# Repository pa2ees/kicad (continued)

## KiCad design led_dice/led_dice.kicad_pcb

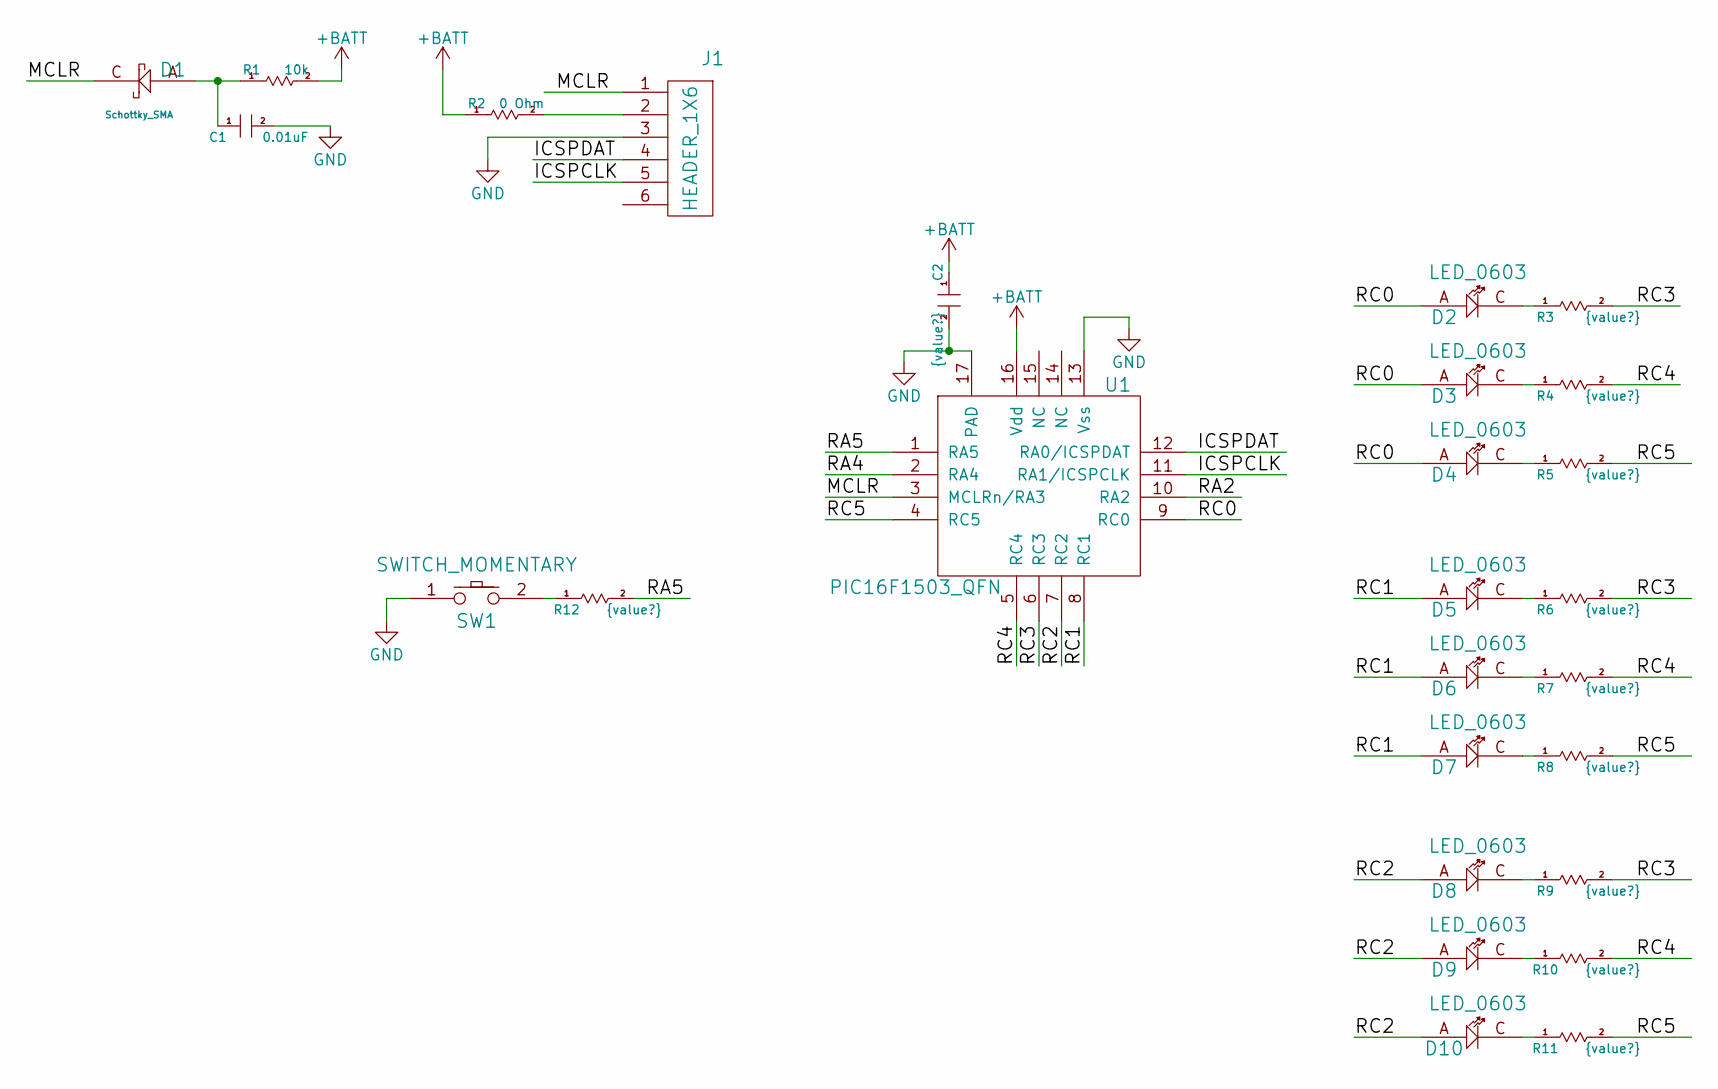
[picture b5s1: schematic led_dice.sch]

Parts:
C1: CAP_0603; C0603
C2: CAP_0603; C0603; MFG_PN {PN}
D1: Schottky_SMA; SMA; MFG_PN {PN}
D2, D3, D4, D5, D6, D7, D8, D9, D10: LED_0603; D0603; MFG_PN {PN}
J1: HEADER_1X6; Header_6-pin_100mil
R1, R2: RES_0603; R0603
R3, R4, R5, R6, R7, R8, R9, R10, R11, R12: RES_0603; R0603; MFG_PN {PN}
SW1: SWITCH_MOMENTARY; TACT-SW_6x6
U1: PIC16F1503_QFN; MFG_PN PIC16F1503-I/MG

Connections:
+BATT: C2.1, R1.2, R2.1, U1.16 (Vdd)
/ICSPCLK: J1.5, U1.11 (RA1/ICSPCLK)
/ICSPDAT: J1.4, U1.12 (RA0/ICSPDAT)
/MCLR: D1.C, J1.1, U1.3 (MCLRn/RA3)
/RA2: U1.10 (RA2)
/RA4: U1.2 (RA4)
/RA5: R12.2, U1.1 (RA5)
/RC0: D2.A, D3.A, D4.A, U1.9 (RC0)
/RC1: D5.A, D6.A, D7.A, U1.8 (RC1)
/RC2: D8.A, D9.A, D10.A, U1.7 (RC2)
/RC3: R3.2, R6.2, R9.2, U1.6 (RC3)
/RC4: R4.2, R7.2, R10.2, U1.5 (RC4)
/RC5: R5.2, R8.2, R11.2, U1.4 (RC5)
GND: C1.2, C2.2, J1.3, SW1.1, U1.13 (Vss), U1.17 (PAD)
unnamed: C1.1, D1.A, R1.1
unnamed: D2.C, R3.1
unnamed: D3.C, R4.1
unnamed: D4.C, R5.1
unnamed: D5.C, R6.1
unnamed: D6.C, R7.1
unnamed: D7.C, R8.1
unnamed: D8.C, R9.1
unnamed: D9.C, R10.1
unnamed: D10.C, R11.1
unnamed: J1.2, R2.2
unnamed: R12.1, SW1.2

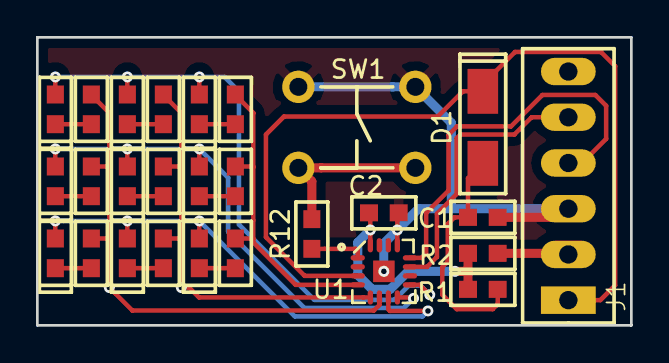
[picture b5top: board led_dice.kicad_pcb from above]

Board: 2 copper layers, 33.0 x 16.0 mm, 27 parts (0 on the bottom side), 24 nets.

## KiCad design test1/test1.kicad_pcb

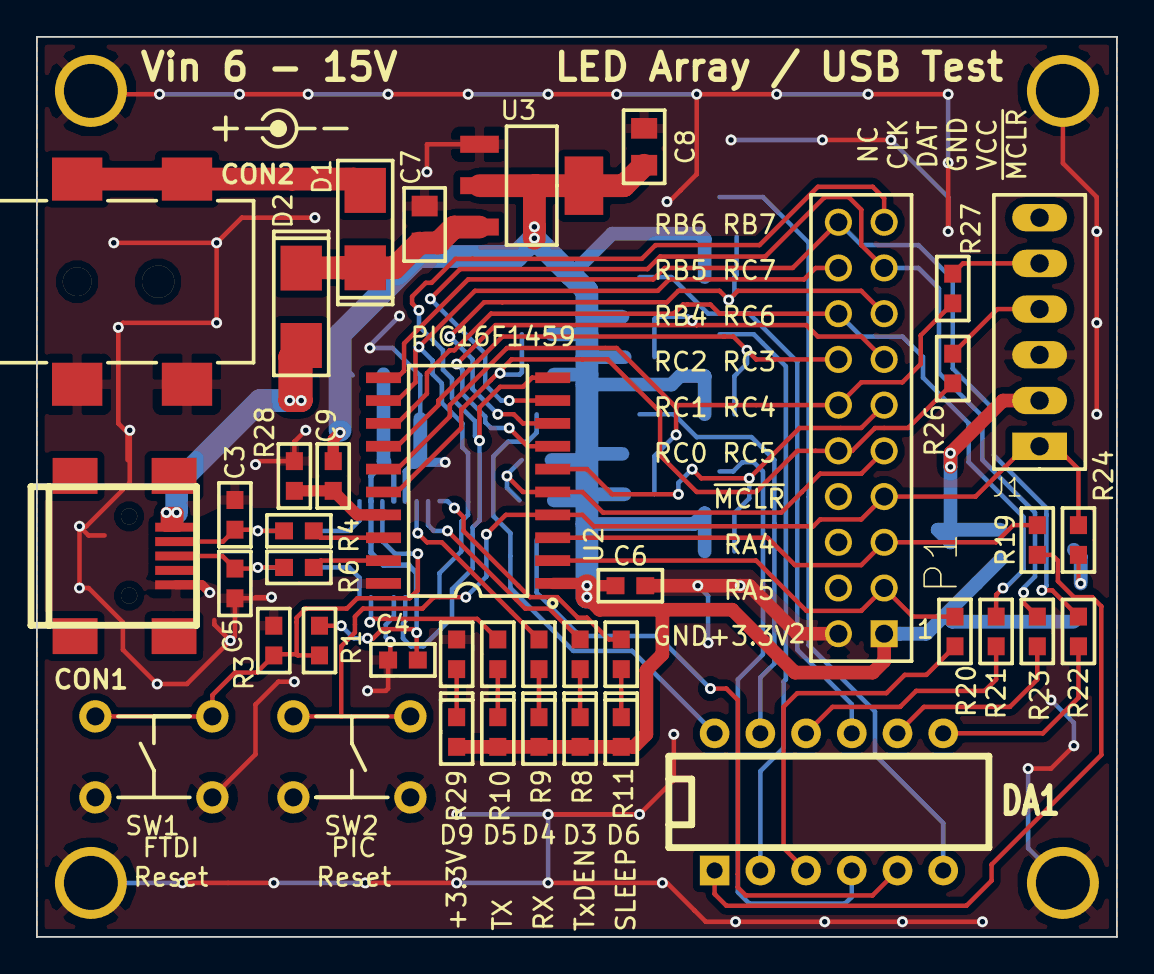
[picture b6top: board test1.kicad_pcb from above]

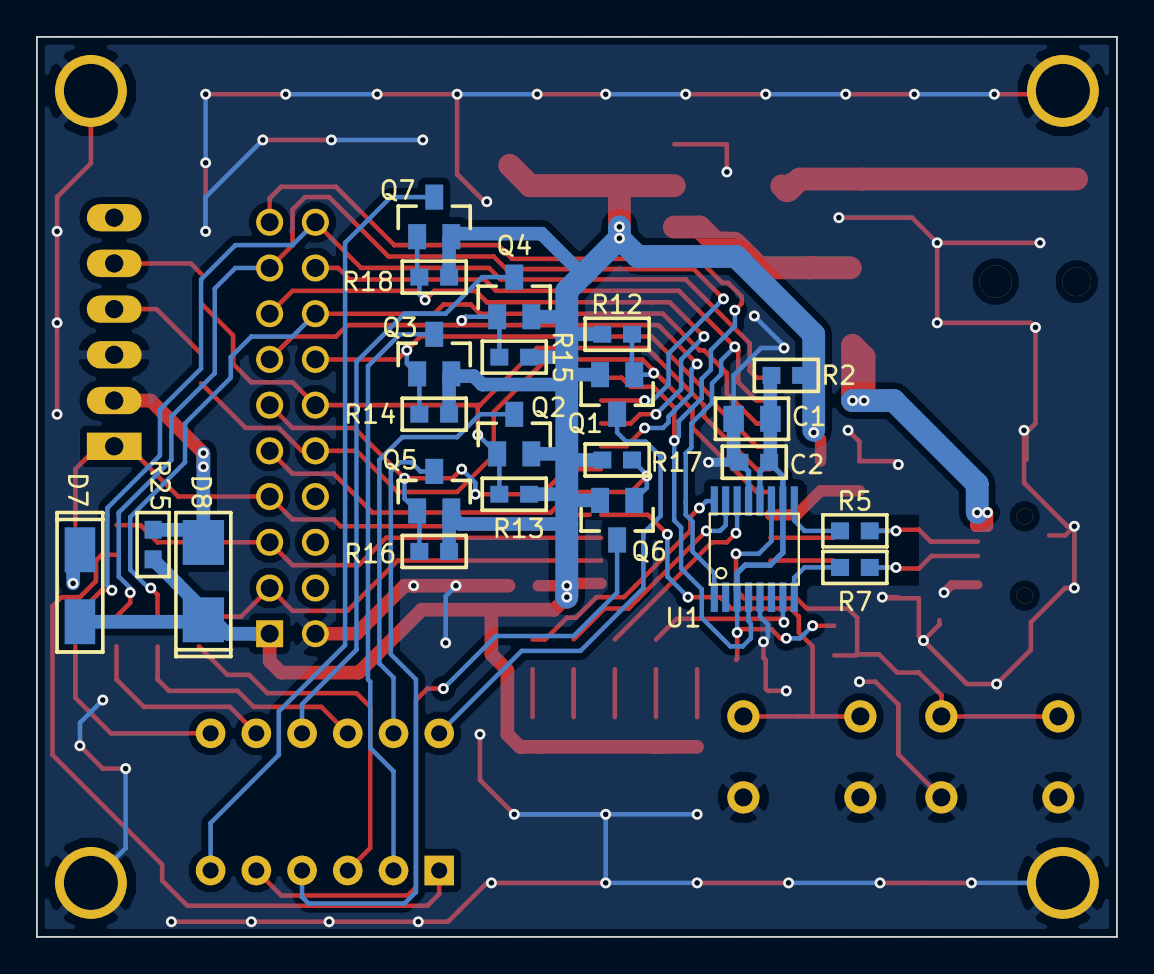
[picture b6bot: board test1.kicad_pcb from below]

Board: 2 copper layers, 60.0 x 50.0 mm, 68 parts (23 on the bottom side), 54 nets.

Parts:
C1, C7, C8: CAP_0805; C0805
C2, C3, C4, C5, C6, C9: CAP_0603; C0603
CON1: USB-MINI-B; USB_MINI_B
CON2: BARREL_JACK; BARREL_JACK_SMT
D1, D2, D8: SCHOTTKY_SMB; SMB
D3, D4, D5, D6, D9: LED_0603; D0603
D7: SCHOTTKY_SMA; SMA
DA1: LED_ARR_7X5_CCOL-AROW; DIP-12_300
J1: HEADER_1X6; Header_6-pin_100mil
M1, M2, M3, M4: MNT-3MM; MNT-3mm
P1: CONN_10X2; Header_10x2_100mil
Q1, Q2, Q3, Q4, Q5, Q6, Q7: MOSFET-P; SOT-23-3
R1, R2, R3, R4, R5, R6, R7, R8, R9, R10, R11, R12, R13, R14, R15, R16, R17, R18, R19, R20, R21, R22, R23, R24, R25, R26, R27, R28, R29: RES_0603; R0603
SW1, SW2: SWITCH_MOMENTARY; TACT-SW_6x6
U1: FT230XS; ssop-16
U2: PIC16F1459_SOIC; SO-20
U3: TLV1117_3.3V; SOT-223

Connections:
+3.3V: C6.2, C8.2, D3.A, D4.A, D5.A, D6.A, D7.A, D8.C, D9.A, P1.1, Q1.S, Q2.S, Q3.S, Q4.S, Q5.S, Q6.S, Q7.S, R2.1, R12.2, R13.2, R14.2, R15.2, R16.2, R17.2, R18.2, R25.1, R28.2, U2.1, U3.2, U3.4
/+3.3V_ftdi: C1.2, C2.2, C4.2, R1.1, R2.2, U1.3, U1.10, U1.12
/A_R1: DA1.12, Q1.D
/A_R2: DA1.11, Q2.D
/A_R3: DA1.2, Q3.D
/A_R4: DA1.9, Q4.D
/A_R5: DA1.4, Q5.D
/A_R6: DA1.5, Q6.D
/A_R7: DA1.6, Q7.D
/C_C1: DA1.1, R19.1
/C_C2: DA1.3, R20.1
/C_C3: DA1.10, R21.1
/C_C4: DA1.7, R22.1
/C_C5: DA1.8, R23.1
/D+: C5.2, CON1.3, R6.1, R7.1
/D+_ftdi: R7.2, U1.8
/D+_micro: R6.2, U2.19
/D-: C3.2, CON1.2, R4.1, R5.1
/D-_ftdi: R5.2, U1.9
/D-_micro: R4.2, U2.18
/ICSPCLK: J1.5, R27.2
/ICSPDAT: J1.4, R26.2
/RA4: P1.5, R19.2, U2.3
/RA5: P1.3, R20.2, U2.2
/RB4: P1.16, R21.2, U2.13
/RB5: P1.18, U1.1, U2.12
/RB6: P1.20, R22.2, U2.11
/RB7: P1.19, U1.4, U2.10
/RC0: P1.10, Q1.G, R12.1, R26.1, U2.16
/RC1: P1.12, Q2.G, R13.1, R27.1, U2.15
/RC2: P1.14, Q3.G, R14.1, U2.14
/RC3: P1.13, Q4.G, R15.1, U2.7
/RC4: P1.11, Q5.G, R16.1, U2.6
/RC5: P1.9, Q6.G, R17.1, U2.5
/RC6: P1.15, Q7.G, R18.1, U2.8
/RC7: P1.17, R23.2, U2.9
/~MCLR: J1.1, P1.7, R24.1, SW2.1, U2.4
GND: C1.1, C2.1, C3.1, C4.1, C5.1, C6.1, C7.1, C8.1, C9.1, CON1.5, CON2.2, CON2.3, J1.3, M1.1, M2.1, M3.1, M4.1, P1.2, R3.1, R29.1, SW1.1, SW2.2, U1.5, U1.13, U2.20, U3.1
unnamed: D3.C, R8.2
unnamed: R8.1, U1.15
unnamed: R9.1, U1.14
unnamed: R10.1, U1.7
unnamed: R11.1, U1.16
unnamed: D4.C, R9.2
unnamed: D5.C, R10.2
unnamed: D6.C, R11.2
unnamed: R1.2, R3.2, SW1.2, U1.11
unnamed: D7.C, R24.2
unnamed: D9.C, R29.2
unnamed: D8.A, J1.2, R25.2
unnamed: C9.2, R28.1, U2.17
PWR_IN: CON2.1, D1.A
USB_PWR: CON1.1, D2.A
Vin: C7.2, D1.C, D2.C, U3.3

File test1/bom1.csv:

CAP_0805,1,"C1",4.7uF
CAP_0603,4,"C2 C4 C6 C9",0.1uF
CAP_0603,2,"C3 C5",47pF
CAP_0805,1,"C7",2.2uF
CAP_0805,1,"C8",10uF
USB-MINI-B,1,"CON1"
BARREL_JACK,1,"CON2"
SCHOTTKY_SMA,1,"D7"
SCHOTTKY_SMB,3,"D1 D2 D8"
LED_0603,2,"D3 D9",150060VS75000
LED_0603,2,"D4 D5",150060BS75000
LED_0603,1,"D6",150060RS75000
LED_ARR_7X5_CCOL-AROW,1,"DA1"
HEADER_1X6,1,"J1"
MNT-3MM,4,"M1 M2 M3 M4"
CONN_10X2,1,"P1"
MOSFET-P,7,"Q1 Q2 Q3 Q4 Q5 Q6 Q7",BSS84
RES_0603,2,"R1 R24",10K
RES_0603,2,"R2 R28",0 Ohms
RES_0603,8,"R3 R12 R13 R14 R15 R16 R17 R18",100K
RES_0603,4,"R4 R5 R6 R7",27R
RES_0603,3,"R8 R11 R29",270
RES_0603,2,"R9 R10",62
RES_0603,5,"R19 R20 R21 R22 R23",240
RES_0603,3,"R25 R26 R27",1K
SWITCH_MOMENTARY,2,"SW1 SW2"
TLV1117_3.3V,1,"U3"
FT230XS,1,"U1"
PIC16F1459_SOIC,1,"U2"

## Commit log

2019-01-26 Adding snippets for easy import to kicad schematics
2019-01-26 Added transceiver test, board built from this commit
2019-01-26 updated libraries
2019-01-26 Not exactly sure what this all is, but committing it anyways
2019-02-06 updated snippets
2019-02-06 First shot of gerbers for sprinkler nodes
2019-02-06 updated gerbers
2019-04-04 Version 1.0 of sprinkler nodes done. Functioning except for valve switch.
2019-04-11 Rev 1.1 Sprinkler Nodes. Added more options for turning on valves
2019-04-11 committing gerbers (rev 1.0) as they were sent to fab house
2019-04-16 Updated part numbers
2019-04-16 Updated libraries and cleanup
2019-04-16 updates to gerber file name
2019-04-16 Added BOM
2019-05-21 added sprinkler node buffer
2023-12-02 Updating accelerometers to new kicad 7
2023-12-02 Add remote temp sensor project
